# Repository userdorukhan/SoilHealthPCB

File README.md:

# 🌱 SoilHealth – Smart Agriculture PCB Project

**SoilHealth** is a smart environmental monitoring system designed as part of the Hope DeCal at UC Berkeley. This project aims to measure key soil and atmospheric parameters to support precision agriculture, gardening, and sustainability efforts. The custom-designed PCB integrates multiple sensors, solar-powered charging, and wireless data transmission via an ESP32 microcontroller.

---

## 🔧 Features

* **Custom PCB Design** for low-power, compact, and modular sensor integration
* **Solar-Powered System** with a Li-ion battery and charging circuit
* **ESP32 Microcontroller** for sensor interfacing and Wi-Fi communication
* **U.FL Antenna Connector** for extended wireless range
* **Data Logging** to Firebase for real-time remote monitoring

---

## 🌡️ Sensors Used

| Sensor  | Measurement                     | Notes                       |
| ------- | ------------------------------- | --------------------------- |
| SEN0193 | Soil Moisture                   | Capacitive, analog output   |
| DS18B20 | Soil Temperature                | Waterproof, 1-Wire protocol |
| BH1750  | Light Intensity                 | Digital I2C sensor          |
| BME280  | Temperature, Humidity, Pressure | I2C protocol                |

---

## ⚡ Power Management

* **Solar Panel Input**
* **Lithium-Ion Battery** charging via onboard circuit
* **Voltage Regulator** to ensure stable 3.3V supply to ESP32 and sensors

---

## 📡 Connectivity

* **Wi-Fi Transmission** via ESP32
* **Firebase Integration** for remote data storage and visualization

---

## 📐 PCB Highlights

* Designed using KiCad
* Double-layer board optimized for low noise and compact routing
* Separate power domain for analog sensors to reduce interference
* Test points for debugging and voltage verification

---

## 🛠️ Future Improvements

* Add onboard SD card logging for offline operation
* Improve power optimization via deep sleep modes
* Add additional sensors (e.g., CO₂, VOC) for advanced monitoring

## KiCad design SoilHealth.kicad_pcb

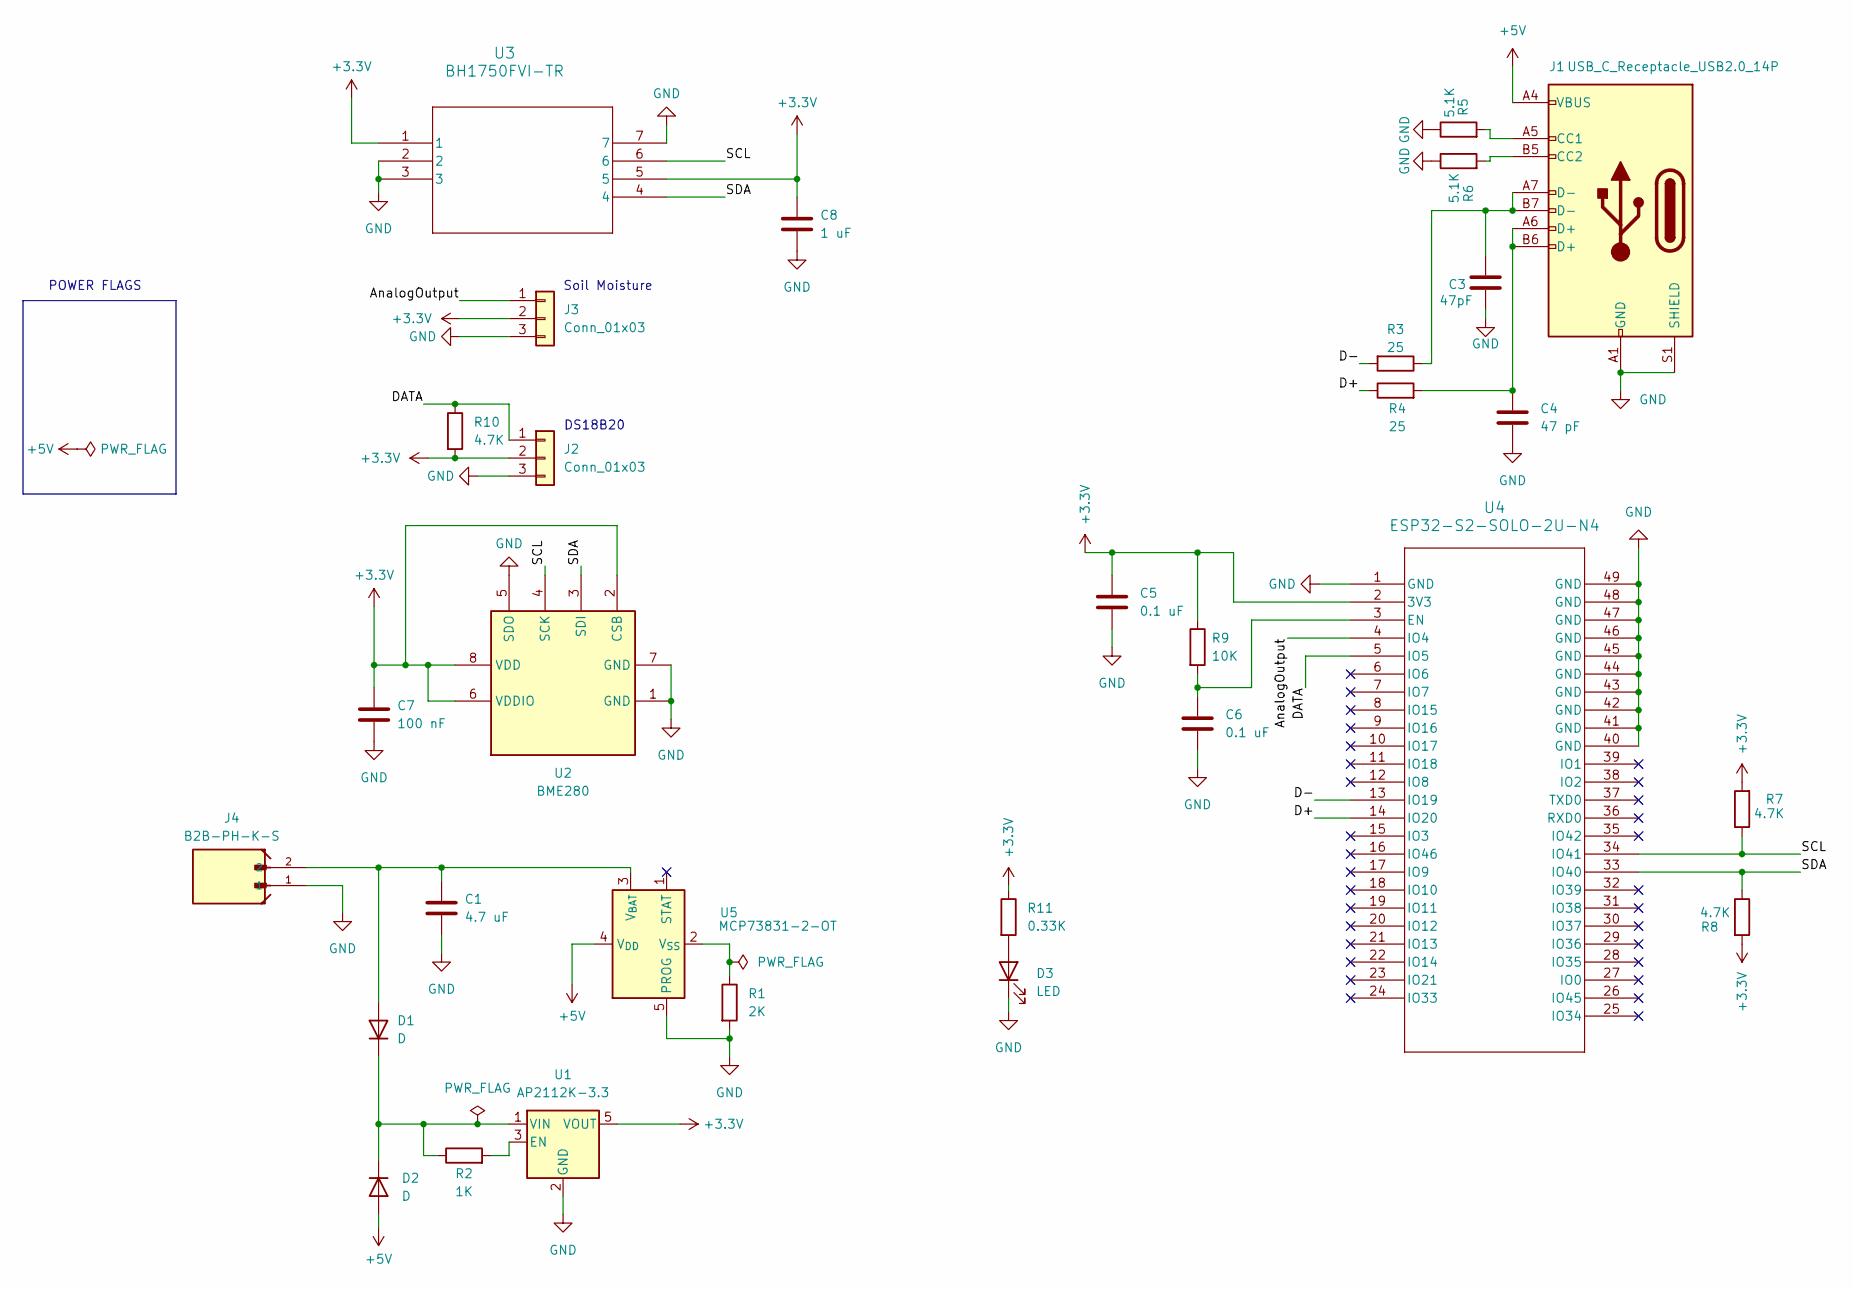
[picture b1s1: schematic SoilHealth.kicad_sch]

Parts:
C1: 4.7 uF; C_0603_1608Metric_Pad1.08x0.95mm_HandSolder
C3: 47pF; C_0603_1608Metric_Pad1.08x0.95mm_HandSolder
C4: 47 pF; C_0603_1608Metric_Pad1.08x0.95mm_HandSolder
C5, C6: 0.1 uF; C_0603_1608Metric_Pad1.08x0.95mm_HandSolder
C7: 100 nF; C_0603_1608Metric_Pad1.08x0.95mm_HandSolder
C8: 1 uF; C_0603_1608Metric_Pad1.08x0.95mm_HandSolder
D1, D2: D; D_SMA
D3: LED; D_0603_1608Metric_Pad1.05x0.95mm_HandSolder
J1: USB_C_Receptacle_USB2.0_14P; USB_C_Receptacle_GCT_USB4105-xx-A_16P_TopMnt_Horizontal
J2: Conn_01x03; PinSocket_1x03_P2.54mm_Vertical
J3: Conn_01x03; PinHeader_1x03_P2.54mm_Vertical
J4: B2B-PH-K-S; BatteryHead
R1: 2K; R_0603_1608Metric_Pad0.98x0.95mm_HandSolder
R2: 1K; R_0603_1608Metric_Pad0.98x0.95mm_HandSolder
R3, R4: 25; R_0603_1608Metric_Pad0.98x0.95mm_HandSolder
R5, R6: 5.1K; R_0603_1608Metric_Pad0.98x0.95mm_HandSolder
R7, R8, R10: 4.7K; R_0603_1608Metric_Pad0.98x0.95mm_HandSolder
R9: 10K; R_0603_1608Metric_Pad0.98x0.95mm_HandSolder
R11: 0.33K; R_0603_1608Metric_Pad0.98x0.95mm_HandSolder
U1: AP2112K-3.3; SOT-23-5
U2: BME280; Bosch_LGA-8_2.5x2.5mm_P0.65mm_ClockwisePinNumbering
U3: BH1750FVI-TR; LightEmmity
U4: ESP32-S2-SOLO-2U-N4; ESP32-S2-SOLO-2U_EXP
U5: MCP73831-2-OT; SOT-23-5

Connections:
+3.3V: C5.1, C7.1, C8.1, J2.2, J3.2, R7.2, R8.2, R9.1, R10.2, R11.1, U1.5 (VOUT), U2.2 (CSB), U2.6 (VDDIO), U2.8 (VDD), U3.1, U3.5, U4.2 (3V3)
+5V: D2.2 (A), J1.A4 (VBUS), J1.A9 (VBUS), J1.B4 (VBUS), J1.B9 (VBUS), U5.4 (V_{DD})
/AnalogOutput: J3.1, U4.4 (IO4)
/D+: R4.1, U4.14 (IO20)
/D-: R3.2, U4.13 (IO19)
/DATA: J2.1, R10.1, U4.5 (IO5)
/SCL: R7.1, U2.4 (SCK), U3.6, U4.34 (IO41)
/SDA: R8.1, U2.3 (SDI), U3.4, U4.33 (IO40)
GND: C1.2, C3.2, C4.2, C5.2, C6.2, C7.2, C8.2, D3.1 (K), J1.A1 (GND), J1.A12 (GND), J1.B1 (GND), J1.B12 (GND), J1.S1 (SHIELD), J2.3, J3.3, J4.1, R1.2, R5.1, R6.1, U1.2 (GND), U2.1 (GND), U2.5 (SDO), U2.7 (GND), U3.2, U3.3, U3.7, U4.1 (GND), U4.40 (GND), U4.41 (GND), U4.42 (GND), U4.43 (GND), U4.44 (GND), U4.45 (GND), U4.46 (GND), U4.47 (GND), U4.48 (GND), U4.49 (GND), U5.5 (PROG)
unnamed: C3.1, J1.A7 (D-), J1.B7 (D-), R3.1
unnamed: C4.1, J1.A6 (D+), J1.B6 (D+), R4.2
unnamed: C1.1, D1.2 (A), J4.2, U5.3 (V_{BAT})
unnamed: D1.1 (K), D2.1 (K), R2.1, U1.1 (VIN)
unnamed: D3.2 (A), R11.2
unnamed: J1.A5 (CC1), R5.2
unnamed: J1.B5 (CC2), R6.2
unnamed: R2.2, U1.3 (EN)
unnamed: C6.1, R9.2, U4.3 (EN)
unnamed: R1.1, U5.2 (V_{SS})

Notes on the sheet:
POWER FLAGS
Soil Moisture
DS18B20

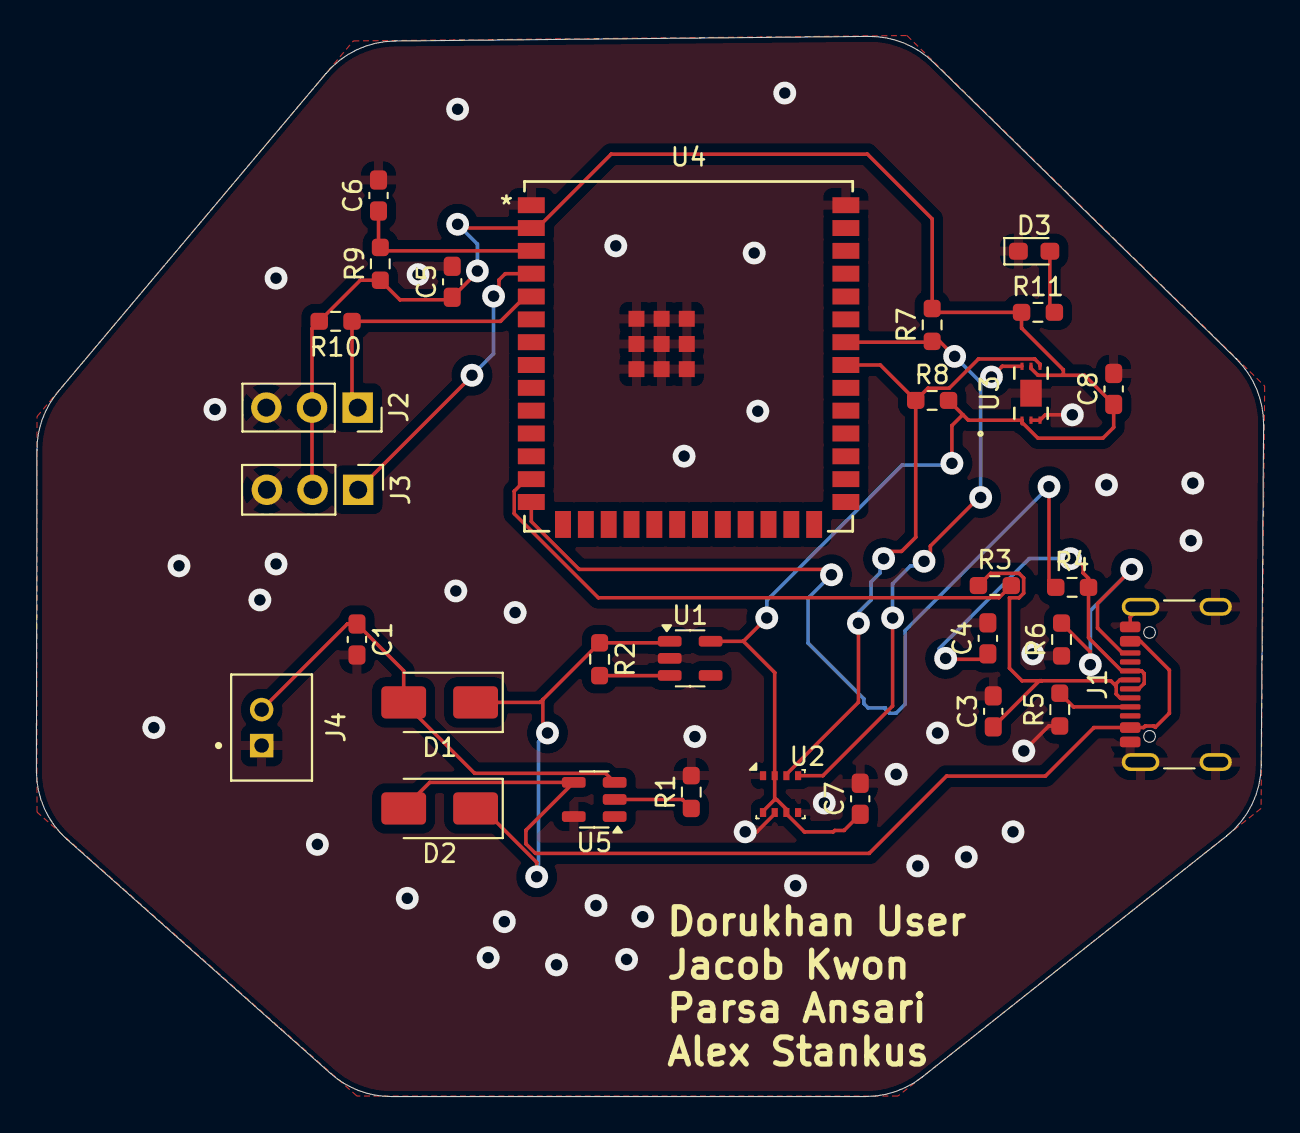
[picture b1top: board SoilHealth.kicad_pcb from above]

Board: 2 copper layers, 68.3 x 59.0 mm, 30 parts (0 on the bottom side), 19 nets.

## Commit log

2025-06-12 All files for the PCB
